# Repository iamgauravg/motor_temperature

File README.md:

# motor_temperature
Monitor temperature and turn on fan if too hot

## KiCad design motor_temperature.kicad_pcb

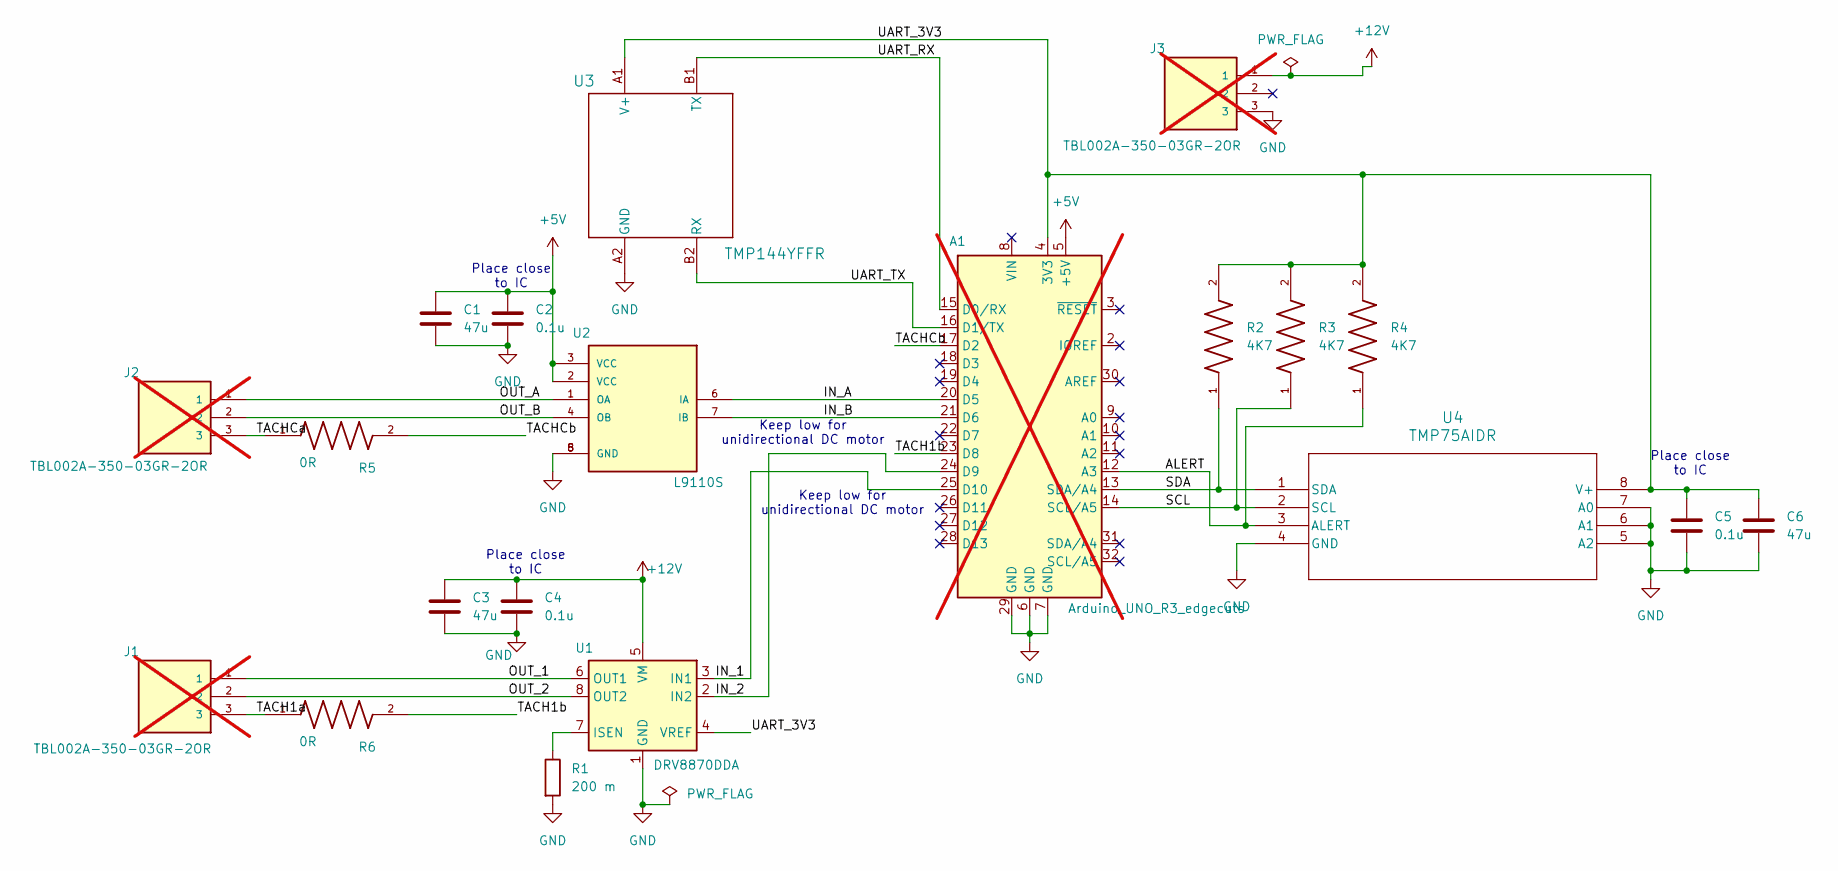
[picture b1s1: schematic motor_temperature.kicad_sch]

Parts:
A1: Arduino_UNO_R3_edgecuts; Arduino_UNO_R3_edgecuts_withoutcourtyard_notabs_nosilkscree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; not fitted
C1, C3, C6: 47u; C_1210_3225Metric_Pad1.33x2.70mm_HandSolder; MPN1 CGA1210X5R476M250RT
C2, C4, C5: 0.1u; C_0603_1608Metric_Pad1.08x0.95mm_HandSolder; MPN1 CGA0603X7R104K250JT
J1, J2, J3: TBL002A-350-03GR-2OR; CUI_TBL002A-350-03GR-2OR; PARTREV 1.0; not fitted
R1: 200 m; R_0603_1608Metric_Pad0.98x0.95mm_HandSolder; MPN1 0603WAF220LT5E
R2, R3, R4: 4K7; RESC3115X65N; PARTREV V3
R5, R6: 0R; RESC3115X65N; PARTREV V3
U1: DRV8870DDA; Texas_HTSOP-8-1EP_3.9x4.9mm_P1.27mm_EP2.95x4.9mm_Mask2.4x3.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; MPN1 DRV8870DDAR
U2: L9110S; SOIC127P599X172-8N; PARTREV NA
U3: TMP144YFFR; YFF0004AAAJ; MPN1 TMP144YFFR
U4: TMP75AIDR; D8; MPN1 TMP75AIDR

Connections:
+5V: A1.5 (+5V), C1.1, C2.1, U2.2 (VCC), U2.3 (VCC)
+12V: C3.1, C4.1, J3.1, U1.5 (VM)
/ALERT: A1.12 (A3), R4.1, U4.3 (ALERT)
/IN_1: A1.25 (D10), U1.3 (IN1)
/IN_2: A1.24 (D9), U1.2 (IN2)
/IN_A: A1.20 (D5), U2.6 (IA)
/IN_B: A1.21 (D6), U2.7 (IB)
/OUT_1: J1.1, U1.6 (OUT1)
/OUT_2: J1.2, U1.8 (OUT2)
/OUT_A: J2.1, U2.1 (OA)
/OUT_B: J2.2, U2.4 (OB)
/SCL: A1.14 (SCL/A5), R3.1, U4.2 (SCL)
/SDA: A1.13 (SDA/A4), R2.1, U4.1 (SDA)
/TACH1a: J1.3, R6.1
/TACH1b: A1.23 (D8), R6.2
/TACHCa: J2.3, R5.1
/TACHCb: A1.17 (D2), R5.2
/UART_3V3: A1.4 (3V3), C5.1, C6.1, R2.2, R3.2, R4.2, U1.4 (VREF), U3.A1 (V+), U4.8 (V+)
/UART_RX: A1.15 (D0/RX), U3.B1 (TX)
/UART_TX: A1.16 (D1/TX), U3.B2 (RX)
GND: A1.6 (GND), A1.7 (GND), A1.29 (GND), C1.2, C2.2, C3.2, C4.2, C5.2, C6.2, J3.3, R1.2, U1.1 (GND), U1.9 (GND), U2.5 (GND), U2.8 (GND), U3.A2 (GND), U4.4 (GND), U4.5 (A2), U4.6 (A1), U4.7 (A0)
unnamed: R1.1, U1.7 (ISEN)

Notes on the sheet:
Place close to IC
Place close to IC
Keep low for unidirectional DC motor

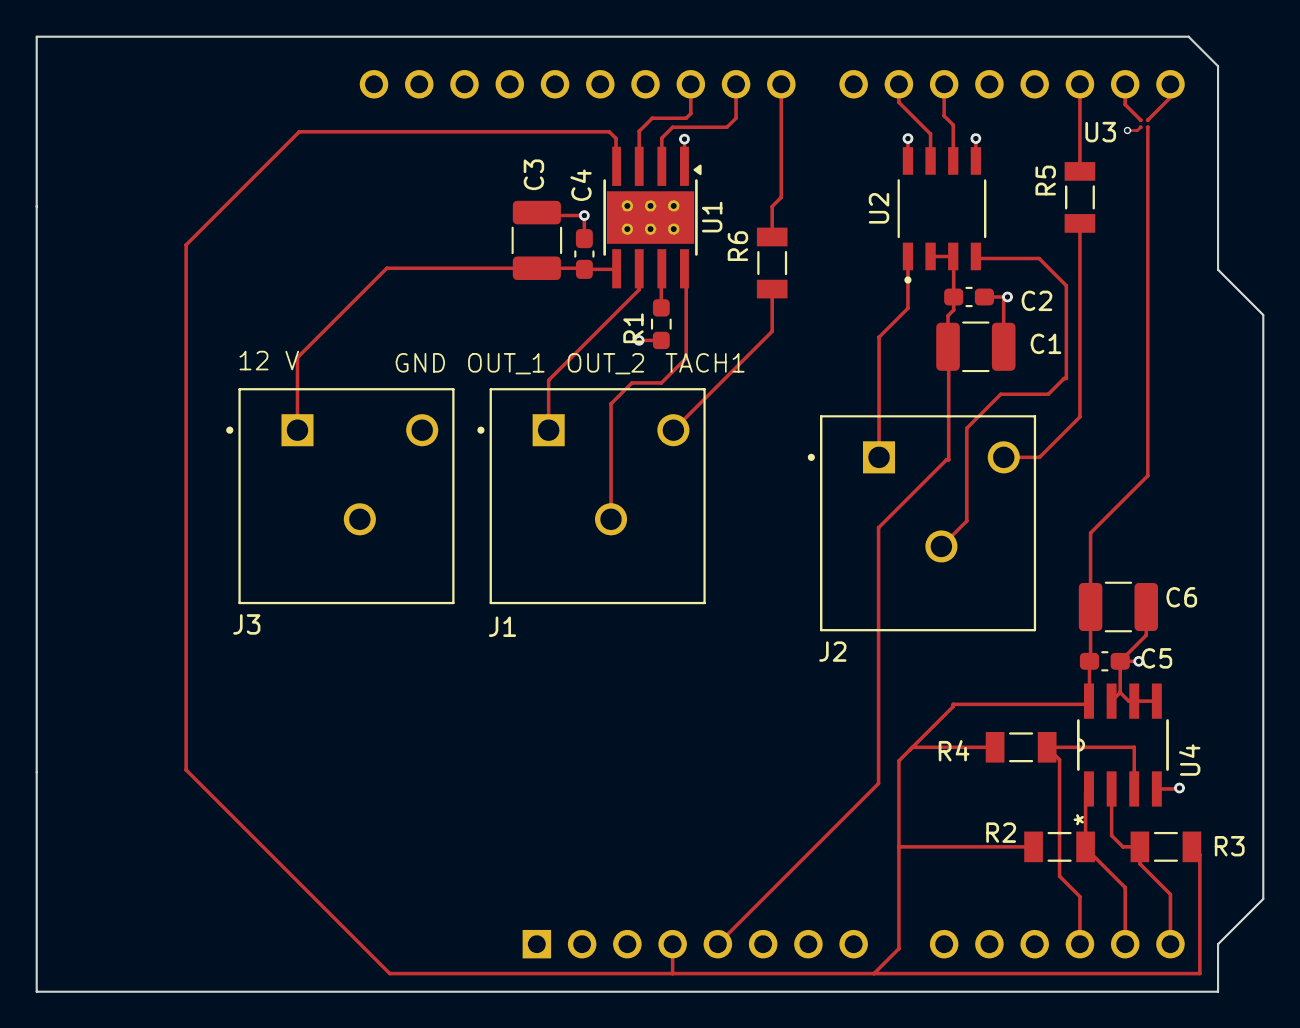
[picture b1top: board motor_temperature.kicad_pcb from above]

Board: 2 copper layers, 68.8 x 53.6 mm, 20 parts (1 on the bottom side), 22 nets.

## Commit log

2025-12-08 Initial commit when layout complete
2025-12-29 Incorporated feedback
    1) Flipped Arduino template for shield to correctly match the STM32 Dicovery board. Rerouted the circuit modules.
    2) Labeled terminals
    3) Removed unnecessary tabs
    4) Added trace for Tachometer with 0 Ohm resistor
    5) Resolved all DRC issues related to silkscreen and clearance
    6) Generated Gerbers, drill files and BOM
